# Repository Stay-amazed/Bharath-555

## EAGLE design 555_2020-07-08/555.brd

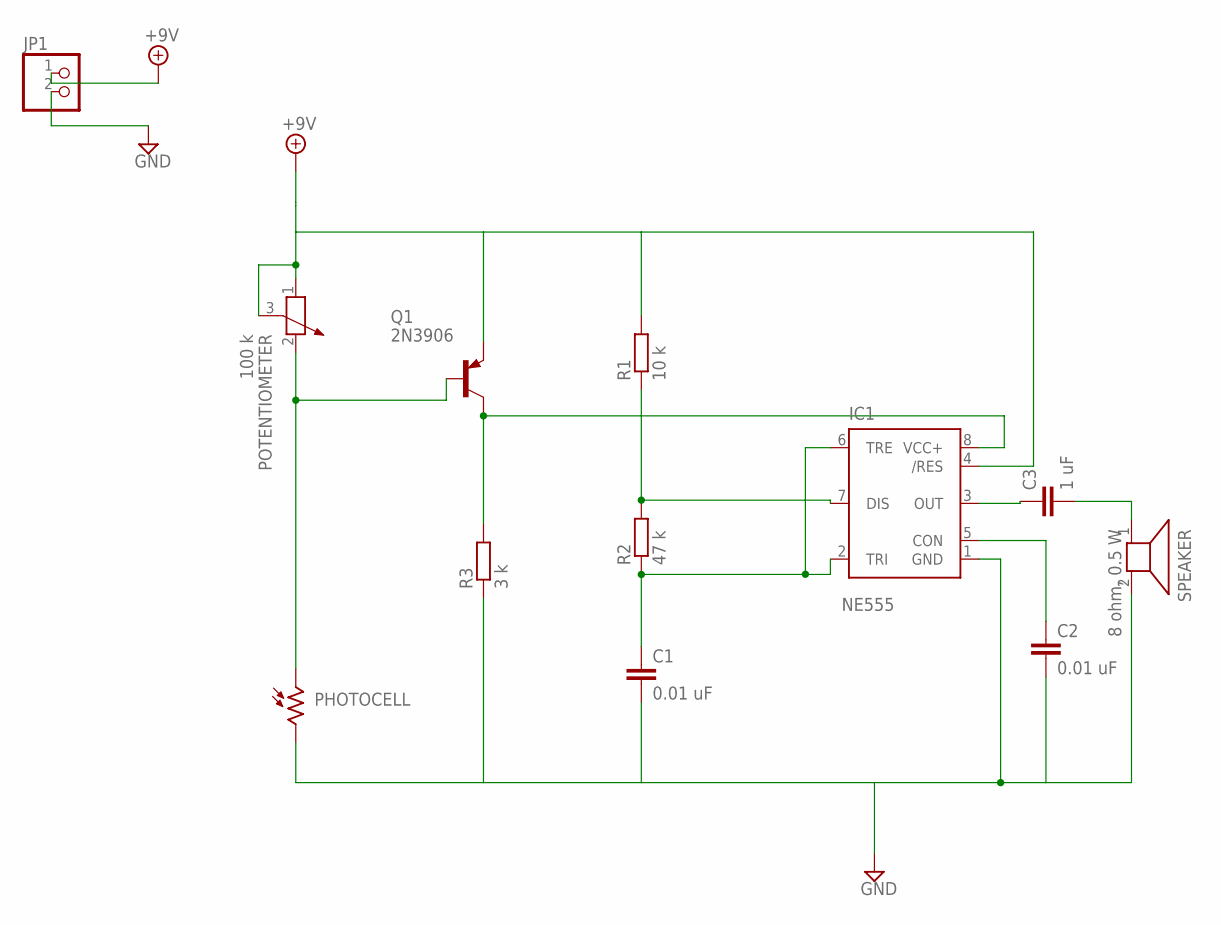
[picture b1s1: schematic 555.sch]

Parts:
C1, C2: 0.01 uF; C025-025X050
C3: 1 uF; C025-025X050
IC1: NE555; DIL-08
JP1: PINHD-1X2; 1X02
PHOTOCELL: PHOTOCELLW55; W55XX_H
POTENTIOMETER: 100 k; PT-10
Q1: 2N3906; TO92
R1: 10 k; 0204/7
R2: 47 k; 0204/7
R3: 3 k; 0204/7
SPEAKER: 8 ohm, 0.5 W; AL60P

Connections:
+9V: IC1.4 (/RES), JP1.1, POTENTIOMETER.1, POTENTIOMETER.3, Q1.3 (E), R1.2
GND: C1.2, C2.2, IC1.1 (GND), JP1.2, PHOTOCELL.2, R3.1, SPEAKER.2
unnamed: C3.1, IC1.3 (OUT)
unnamed: C3.2, SPEAKER.1
unnamed: C2.1, IC1.5 (CON)
unnamed: IC1.7 (DIS), R1.1, R2.2
unnamed: C1.1, IC1.2 (TRI), R2.1
unnamed: IC1.8 (VCC+), Q1.1 (C), R3.2
unnamed: PHOTOCELL.1, POTENTIOMETER.2, Q1.2 (B)

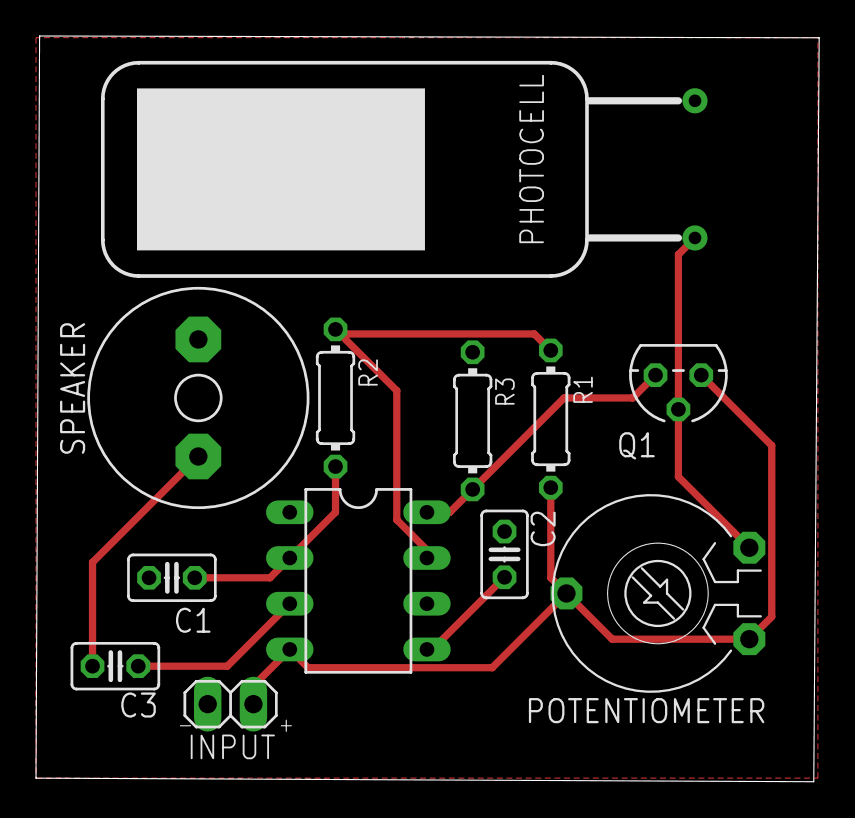
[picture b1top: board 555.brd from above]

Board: 2 copper layers, 43.5 x 41.4 mm, 12 parts (0 on the bottom side), 9 nets.

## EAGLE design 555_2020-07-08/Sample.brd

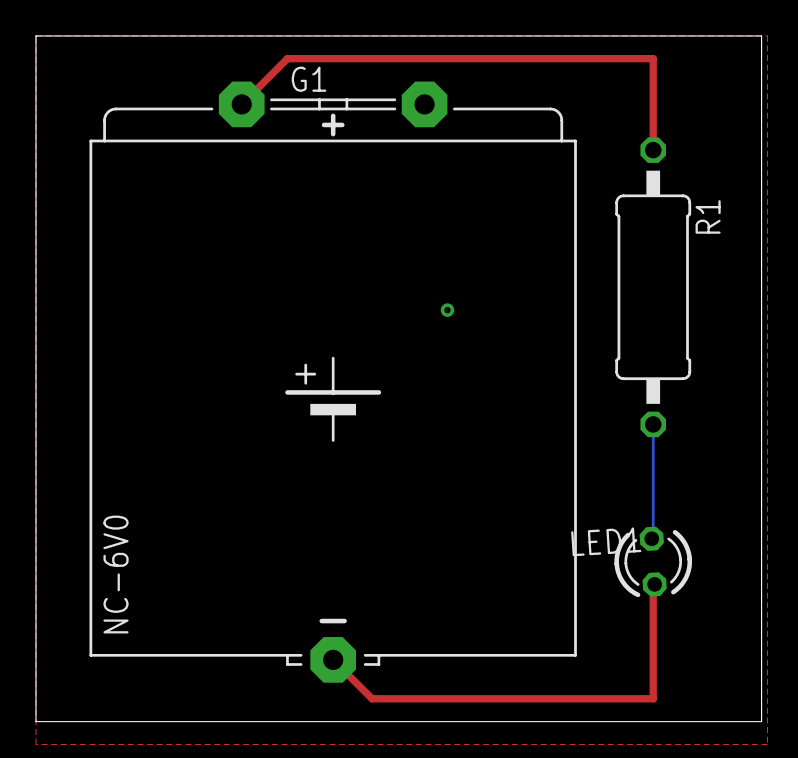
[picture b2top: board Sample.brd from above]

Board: 2 copper layers, 40.3 x 38.1 mm, 3 parts (0 on the bottom side), 3 nets.

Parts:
G1: 5V110R
LED1: Yellow; LED3MM
R1: 330 ohm; 0411/15

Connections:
unnamed: G1.+, R1.1
unnamed: LED1.K, R1.2
unnamed: G1.-, LED1.A

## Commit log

2020-07-09 Bharath-555
